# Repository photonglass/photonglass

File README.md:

日本語 | [English](README.en.md)

# PHOTON GLASS

一人称のカメラで捉えるイメージから，音などのフィードバックでユーザーにインタラクションする，メガネ型のデバイス〈PHOTON GLASS〉のハードウェアデータです。
PHOTON GLASS は、文字を読み上げるメガネOTON GLASS ver5 を元にしながら、自作の容易さや改変性を高め、ツールキットとして新しく開発したものです。
基板2枚（メイン基板・カメラ基板）の設計データ、3Dプリンターで造形できる本体とカメラユニットの筐体、電源ケーブルのカバー、本体のプログラム、組み立てとセットアップの手順を公開しています。
ここで公開しているプログラムは、PHOTON GLASS のサンプル実装のひとつです。一人称カメラで捉えた文字を読み上げる（画像から文字を認識し、音声で読み上げる）機能を実行します。

## 中身

| フォルダ | 内容 | 開けるソフト |
|---|---|---|
| [`hardware/`](hardware/README.md) | 基板2枚の概要、ファイルの開き方、元設計からの変更 | — |
| [`hardware/main-board/`](hardware/main-board) | メイン基板（Raspberry Pi Zero 2 W に載る音声・ボタン基板） | KiCad 9 以降 / Fusion（Eagle形式） |
| [`hardware/camera-board/`](hardware/camera-board) | カメラ基板（HDMIケーブルでメイン基板とつながる） | KiCad 9 以降 / Fusion（Eagle形式） |
| [`enclosure/main-body/`](enclosure/main-body) | 本体の筐体（ボディ前面・背面・側面、メインボタン、サブボタン、状態ランプのレンズ） | F3D（Fusion）/ STEP（FreeCAD など）/ STL・3MF（スライサー） |
| [`enclosure/camera-unit/`](enclosure/camera-unit) | カメラユニットの筐体・メガネ用アタッチメント | STEP（Fusion・FreeCAD など）/ STL・3MF（スライサー）/ Python（CadQuery） |
| [`enclosure/usb-power-cable/`](enclosure/usb-power-cable) | モバイルバッテリーからメイン基板へ給電するケーブルの作り方（配線・部品）と、USB プラグのカバー | STEP / STL / Python（CadQuery） |
| [`software/`](software) | 本体プログラムと効果音。普段使うのは `main_async.py`、仕組みを学ぶなら流れの読みやすい `main_seq.py`（違いは [`software/README.md`](software/README.md)） | Python 3（Raspberry Pi） |
| [`software/test/`](software/test) | 組み立て後の動作テスト用スクリプト（Raspberry Pi で実行） | Python 3 |
| [`docs/`](docs) | 組み立てガイド（[`BUILD_GUIDE.md`](docs/BUILD_GUIDE.md)）、Raspberry Pi のセットアップ（[`SETUP_RASPBERRY_PI.md`](docs/SETUP_RASPBERRY_PI.md)）、部品リスト（[`parts_list.md`](docs/parts_list.md)：データシート・回路記号の照合結果） | — |

## はじめての人へ
- **まず読む**：[`docs/BUILD_GUIDE.md`](docs/BUILD_GUIDE.md) に、発注から動かすまでの作業の順番と、それぞれで読むドキュメントをまとめています。
- **基板を作る**：[`hardware/JLCPCB_ORDERING.md`](hardware/JLCPCB_ORDERING.md) の手順で、JLCPCB に部品実装まで発注できます（ガーバー・部品表・部品配置ファイル付き）。
- **筐体を印刷する**：本体は [`enclosure/main-body/README.md`](enclosure/main-body/README.md)、カメラユニットは [`enclosure/camera-unit/README.md`](enclosure/camera-unit/README.md) に、印刷設定（Bambu Lab A1 / PETG）と組み立て手順があります。
- **Raspberry Pi を準備する**：[`docs/SETUP_RASPBERRY_PI.md`](docs/SETUP_RASPBERRY_PI.md) に、OS の書き込みから動作テスト、自動起動までの手順があります。
- **設計を変える**：基板は KiCad か Fusion で、筐体は STEP を CAD に読み込んで編集します（本体は Fusion の元データ `.f3d` もあります。カメラユニットと電源ケーブルのカバーは、`src/` の Python スクリプトの数値を変えて作り直すこともできます）。

## 質問・不具合の報告

質問や不具合の報告は、GitHub の Issues で受け付けています。
https://github.com/photonglass/photonglass/issues

## 憲法
PHOTON GLASS の理念と利用、名称、特許については、[憲法（`CHARTER.md`）](CHARTER.md)に定めています。

## ライセンス
Copyright (C) 株式会社オトングラス

対象ごとに、次のライセンスで公開しています。

| 対象 | 含まれるもの | ライセンス | 全文 |
|---|---|---|---|
| ソフトウェア | `software/` のプログラム（`main_async.py`・`main_seq.py`・`test/` など） | GNU General Public License v3.0（GPL-3.0-only） | [`LICENSE`](LICENSE) |
| ハードウェア | `hardware/`（基板の KiCad・Eagle データ、BOM・CPL、ガーバーを作るスクリプト `hardware/tools/gerbgen.py`）、`enclosure/`（筐体の CadQuery スクリプトと設計データ。本体の Fusion の元データ `.f3d` を含む）と、それらの生成物（ガーバー、STL・STEP・3MF）。**例外**：README・写真・画像と `hardware/JLCPCB_ORDERING.md` は除く（ドキュメント・写真・画像として CC BY-SA 4.0） | CERN Open Hardware Licence Version 2 - Strongly Reciprocal（CERN-OHL-S v2） | [`LICENSE-HARDWARE`](LICENSE-HARDWARE) |
| ドキュメント・写真・画像 | `docs/`、`CHARTER.md`、`CONTRIBUTING.md`、各フォルダの `README.md`、`hardware/JLCPCB_ORDERING.md`、Issue のテンプレート（`.github/ISSUE_TEMPLATE/`）、写真・画像（各フォルダの `images/` など） | クリエイティブ・コモンズ 表示-継承 4.0 国際（CC BY-SA 4.0） | 公式テキスト：[日本語](https://creativecommons.org/licenses/by-sa/4.0/legalcode.ja)・[English](https://creativecommons.org/licenses/by-sa/4.0/legalcode.en) |
| サウンド | `software/sound/` の効果音 | CC BY-SA 4.0 | 同上 |

- 各 README、写真・画像、`hardware/JLCPCB_ORDERING.md` は、`hardware/`・`enclosure/`・`software/` の中にあっても CC BY-SA 4.0 です。`software/sound/` も、`software/` の中にありますが CC BY-SA 4.0 です。
- 文書の英語版（`README.en.md`・`CHARTER.en.md`・`hardware/JLCPCB_ORDERING.en.md` など、名前の末尾が `.en.md` のファイル）も、日本語版と同じく CC BY-SA 4.0 です。

### CC BY-SA 4.0 のクレジット表記
ドキュメント・写真・画像・サウンドは、株式会社オトングラスが CC BY-SA 4.0 で提供しています。全文のファイルはこのリポジトリに入れていないので、公式テキスト（[日本語](https://creativecommons.org/licenses/by-sa/4.0/legalcode.ja)・[English](https://creativecommons.org/licenses/by-sa/4.0/legalcode.en)）を見てください。

使うときは、次のようにクレジットを表記してください。改変したときは、改変したことも書いてください。
```
PHOTON GLASS（Copyright (C) 株式会社オトングラス）
https://github.com/photonglass/photonglass
CC BY-SA 4.0 https://creativecommons.org/licenses/by-sa/4.0/
```

### かんたんな説明
正確な条件は、各ライセンスの全文を見てください。

**できること**
- 誰でも無料で、このデータで基板や筐体を作り、使い、売ることができます。
- 自由に改変できます。

**守ること**
- 作ったもの・改変したものを人に配ったり売ったりするときは、元と同じライセンスで公開する。
  - ソフトウェアとハードウェアは、受け取った人がソース（プログラム・設計データ）を手に入れられるようにする。ハードウェアの場合は、ソースを渡すか、ソースの置き場所を知らせる。
- 著作権表示とライセンスの表示を消さない。改変した場合は、いつ・どこを変えたかを書く。
- ドキュメント・写真・画像・サウンドを使うときは、上のクレジットを表記する。

**その他**
- 無保証です（作ったものが動かなくても、作者は責任を負いません）。
- 自分で使うだけなら、改変したデータを公開する義務はありません。
- 特許の扱いは、憲法の[「3. 特許について」](CHARTER.md#3-特許について)を見てください。

### 商用ライセンス
クローズドな製品への組み込みなど、各ライセンスの条件と異なる利用を希望する場合は、商用ライセンスを個別に契約できます。問い合わせはこちら：https://note.com/keisukeshimakage/n/nef3c9957ae25

### 含まれていないもの
- 部品メーカーや EasyEDA/LCSC が配布している部品の3Dモデル（再配布の条件がはっきりしないため）。基板の3D形状は KiCad や Fusion の3Dビューで確認してください。
- Google Cloud の API キー（各自で用意して、プログラムと同じフォルダの `api_key.txt` に書く。書き方は [`software/README.md`](software/README.md#動かし方)）。

### クレジット
**PHOTON GLASS（2026年）**
- 回路・基板設計、ドキュメンテーション：山中将治（Masaharu Yamanaka）
- プロダクトデザイン：小松靖知（Yasutomo Komatsu）
- プログラミング：石塚日向（Hinata Ishizuka）
- アドバイジング：須田拓也（Hiroya Suda）、高橋卓久真（Takuma Takahashi）、陳冠宇（Chen Kuan-Yu）

**OTON GLASS ver5（2019年）― PHOTON GLASSの元となったモデル**
- エンジニアリング：宮下恵太（Keita Miyashita）
- サーバーサイドエンジニアリング：鶴岡秀樹（Hideki Tsuruoka）
- プロダクトデザイン：佐野友優（Tomomasa Sano）
- サウンドデザイン：田中堅大（Kenta Tanaka）

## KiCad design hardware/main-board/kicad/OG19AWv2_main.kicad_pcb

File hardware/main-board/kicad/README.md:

日本語 | [English](README.en.md)

# KiCad 9 プロジェクト（メイン基板）

`OG19AWv2_main.kicad_pro` をダブルクリックすると、回路図と基板が開きます。
`../eagle/` の Eagle データを KiCad 9.0 で読み込んで作ったものです。
KiCad 10 以降でも開けますが、保存するとファイルが新しい形式になり、KiCad 9 では開けなくなります。

## Eagle 版との照合（2026-11-12）
| 項目 | 結果 |
|---|---|
| 接続（ネット50本、全パッド） | Eagle 版・回路図・基板の3つで一致 |
| 配線 / ビア / 外形 | 632本 / 125個 / 79 × 42 mm で Eagle 版と同じ |
| ベタ | AGND・DGND を表裏に（計4枚）、充填済み |
| DRC（クリアランス・未配線） | エラー 0 |

### 読み込み後に直したところ
- 基板のネット名を回路図のネット名にそろえた（Eagle の `N$1` などを KiCad 形式の名前に）。
- 標準のクリアランスを 0.2 → **0.15 mm** に変更（元の設計の最小間隔 6 mil = 0.1524 mm に合わせた）。
- 回路図の部品と基板のフットプリントの対応を修正（`R0603` → `R0603_334`、`C0603` → `C0603_334`）。
- 基板のフットプリントの「値」を回路図にそろえた（ボタン3個・コネクタ2個）。

### 部品番号の違い
KiCad の決まり（部品番号は「文字＋数字」）のため、いくつかの部品番号に `0` が付いています。JLCPCB 用の BOM/CPL や説明書は Eagle 版の名前のままです。
| Eagle / BOM・CPL | KiCad |
|---|---|
| PCM5102A | PCM5102A0 |
| SW_MAIN / SW_SUB / SW_UP / SW_DOWN | SW_MAIN0 / SW_SUB0 / SW_UP0 / SW_DOWN0 |
| SPK | SPK0 |
| 5V | UNK5V0 |

### 残っている警告（問題なし）
- 使っていないピンが未接続：Raspberry Pi の40ピンのうち使っていない GPIO と GND、HDMI（CN3）の 11・17・19番。元の設計どおり。
- `UNK_HOLE_0/1`：取り付け穴（非メッキ穴）。回路図に部品がないため「余計なフットプリント」と表示される。
- 40ピンの25番（AGND）の表面側サーマルのスポークが1本：裏面と配線でつながっているので問題なし。
- VR1 まわりの 0.9 mm の短い配線の切れ端：元の設計にあったもの。
- シルクの重なり・文字の大きさ：Eagle のシルク設定をそのまま引き継いだもの（JLCPCB は自動で調整する）。

## DRC の結果（2026-11-25、シルクの文字を大きくしたとき）
KiCad 9.0.8 で、すべての重要度（エラーと警告）と回路図との照合を有効にして実行しました。
| 項目 | 結果 |
|---|---|
| エラー | 1件（上の「40ピンの25番のサーマル」。前からあるもの） |
| 警告 | 83件（変更前 128件。新しく増えたものはなし） |
| 未配線 | 0 |
| 回路図との照合 | 26件（ネット名の表記の違いと取り付け穴。変更前と同じ） |

このとき、次の2つを直しました。
- 表面のシルクの「github.com/photonglass/photonglass / CERN-OHL-S v2」と「PHOTON GLASS / 2026 / PB-4」を、文字の高さ 1.0 mm・線の太さ 0.16 mm にした（JLCPCB の最小値は高さ 1.0 mm・線の太さ 0.153 mm）。Eagle のデータも同じく直してある。
- Eagle の線幅 0 の補助線（基板全体を区切る縦横の線、8本）が、KiCad では表面のシルク（線幅 0.1 mm）として読み込まれていたので、印刷されない User.Drawings レイヤーに移した。Eagle からガーバーを作るスクリプトはこの線を出力しないので、`../gerber/` の zip には元から入っていない。KiCad でガーバーを出力したときにだけ、この線が印刷されていた。

## ガーバーの出力
「ファイル → 製造用ファイル出力 → ガーバー」と「ドリルファイル」で出力し、1つの zip にまとめます。
基板を直さない場合は、`../gerber/` の zip をそのまま使ってください。
`../gerber/` の zip は、Eagle のデータからスクリプトで作ったものです（[`../../JLCPCB_ORDERING.md` の「ガーバーについて」](../../JLCPCB_ORDERING.md#ガーバーについて)）。KiCad で出力すると、ベタGNDの広がり方（基板の端や穴からの間隔）とシルクの文字の形が、この zip と少し変わります。

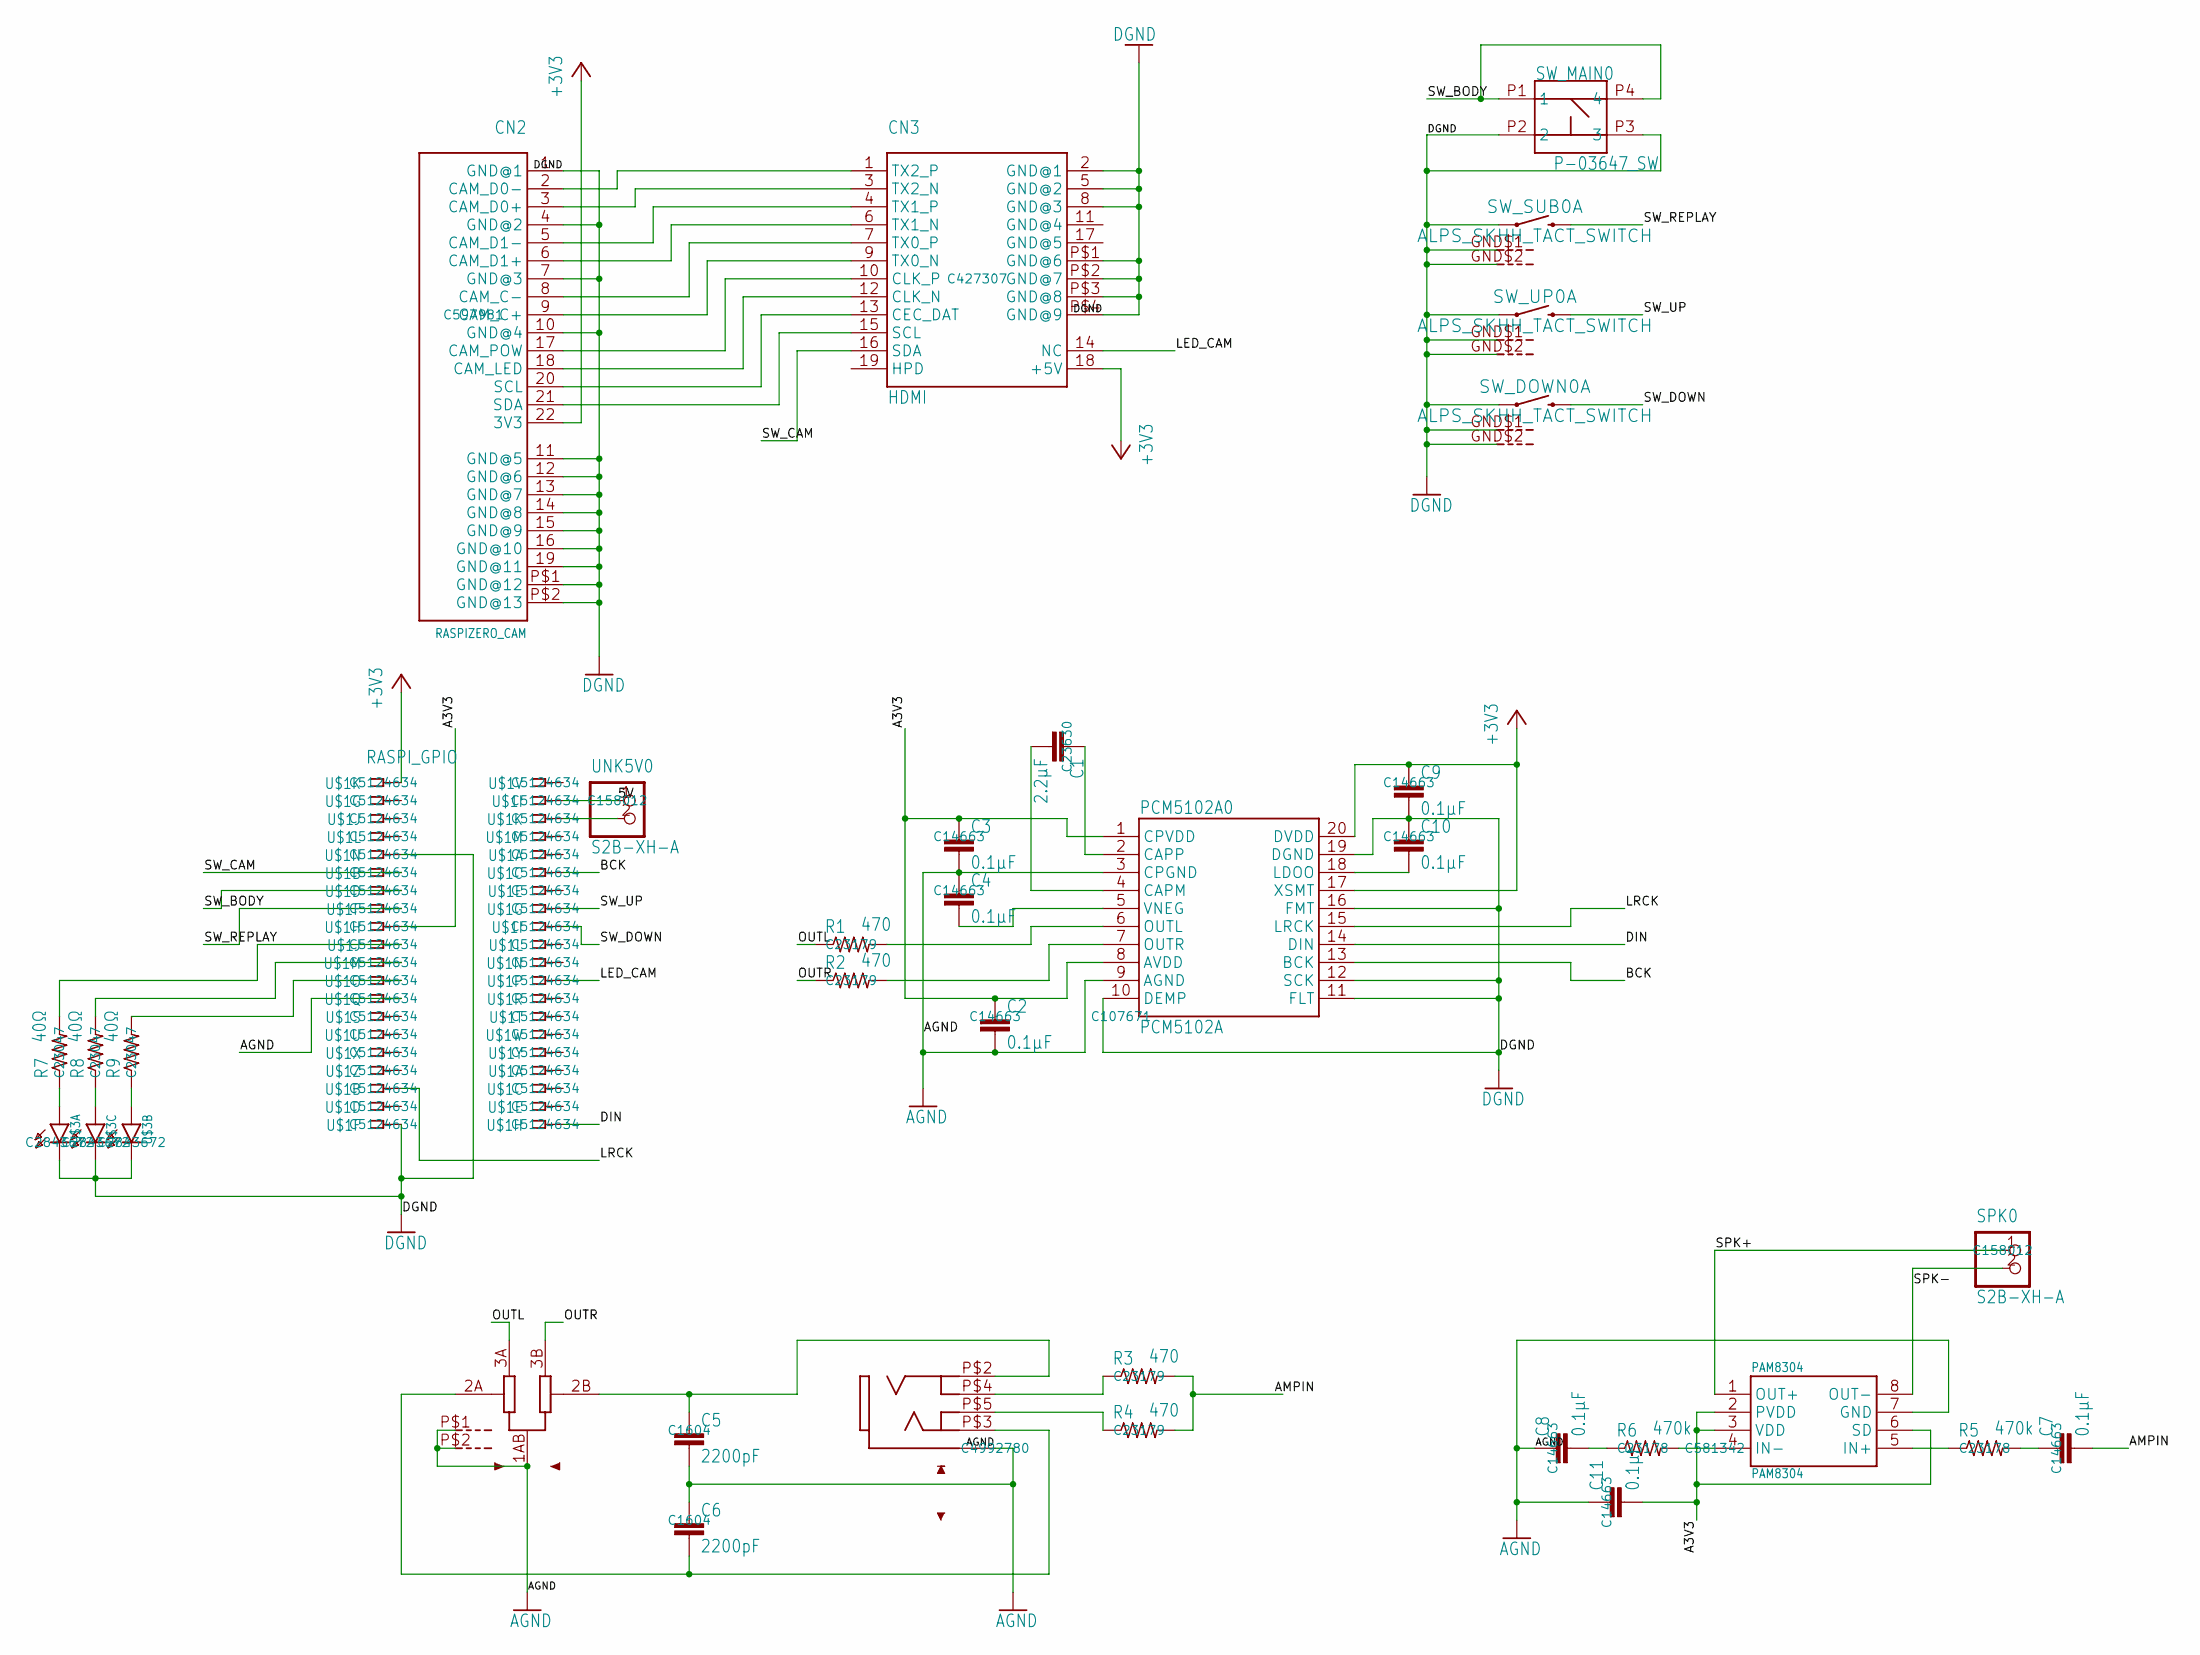
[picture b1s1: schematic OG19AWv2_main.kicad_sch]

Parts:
C1: 2.2μF; C0603_334; LCSC C23630
C2, C3, C4, C7, C8, C9, C10, C11: 0.1μF; C0603_334; LCSC C14663
C5, C6: 2200pF; C0603_334; LCSC C1604
CN1: SWICHCRAFT_3.5MM_PHONE_JACK; SJ-43516-SMT; LCSC C4992780
CN2: RASPIZERO_CAM; FH12-22S-0.5SH; LCSC C597981
CN3: HDMI; LCSC C427307
PAM8304: PAM8304; MSOP8; LCSC C581342
PCM5102A0: PCM5102A; SSOP20; LCSC C107671
R1, R2, R3, R4: 470; R0603_334; LCSC C23179
R5, R6: 470k; R0603_334; LCSC C23178
R7, R8, R9: 40Ω; R0603_334; LCSC C23047
SPK0: S2B-XH-A; B2B-XH-A; LCSC C158012
SW_DOWN0: ALPS_SKHH_TACT_SWITCH; SKHH_SIDEPUSH; MPN Alps SKHHLPA010
SW_MAIN0: P-03647_SW; SW; MPN Cosland TS-0606-F-N-RED
SW_SUB0: ALPS_SKHH_TACT_SWITCH; SKHH_SIDEPUSH; MPN Alps SKHHLPA010
SW_UP0: ALPS_SKHH_TACT_SWITCH; SKHH_SIDEPUSH; MPN Alps SKHHLPA010
U$1: RASPI_GPIO; SSW-120-02-G-D; LCSC C5124634
U$3: KPF-3236SURKMGKPBC; S6-3528RGBTA; LCSC C2843672
UNK5V0: S2B-XH-A; B2B-XH-A; LCSC C158012
VR1: ALPS_RK10J; RK10J_DIP; MPN R1001G16T2B-B10K

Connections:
+3V3: C9.1, CN2.22 (3V3), CN3.18 (+5V), PCM5102A0.17 (XSMT), PCM5102A0.20 (DVDD), U$1.1
/5V: U$1.4, UNK5V0.1
/A3V3: C2.1, C3.1, C11.2, PAM8304.2 (PVDD), PAM8304.3 (VDD), PAM8304.6 (SD), PCM5102A0.1 (CPVDD), PCM5102A0.8 (AVDD), U$1.17
/AMPIN: C7.2, R3.2, R4.2
/BCK: PCM5102A0.13 (BCK), U$1.12
/DIN: PCM5102A0.14 (DIN), U$1.40
/LED_CAM: CN3.14 (NC), U$1.24
/LRCK: PCM5102A0.15 (LRCK), U$1.35
/OUTL: R1.1, VR1.3A
/OUTR: R2.1, VR1.3B
/SPK+: PAM8304.1 (OUT+), SPK0.1
/SPK-: PAM8304.8 (OUT-), SPK0.2
/SW_BODY: SW_MAIN0.P1 (1), SW_MAIN0.P4 (4), U$1.13
/SW_CAM: CN3.16 (SDA), U$1.11
/SW_DOWN: SW_DOWN0.P$2 (2), U$1.18
/SW_REPLAY: SW_SUB0.P$2 (2), U$1.15
/SW_UP: SW_UP0.P$2 (2), U$1.16
AGND: C2.2, C3.2, C4.1, C5.2, C6.1, C8.1, C11.1, CN1.P$1, CN1.P$6, PAM8304.7 (GND), PCM5102A0.3 (CPGND), PCM5102A0.9 (AGND), U$1.25, VR1.1AB, VR1.P$1 (G), VR1.P$2 (G)
DGND: C9.2, C10.1, CN2.1 (GND@1), CN2.4 (GND@2), CN2.7 (GND@3), CN2.10 (GND@4), CN2.11 (GND@5), CN2.12 (GND@6), CN2.13 (GND@7), CN2.14 (GND@8), CN2.15 (GND@9), CN2.16 (GND@10), CN2.19 (GND@11), CN2.P$1 (GND@12), CN2.P$2 (GND@13), CN3.2 (GND@1), CN3.5 (GND@2), CN3.8 (GND@3), CN3.P$1 (GND@6), CN3.P$2 (GND@7), CN3.P$3 (GND@8), CN3.P$4 (GND@9), PCM5102A0.10 (DEMP), PCM5102A0.11 (FLT), PCM5102A0.12 (SCK), PCM5102A0.16 (FMT), PCM5102A0.19 (DGND), SW_DOWN0.GND$1 (G), SW_DOWN0.GND$2 (G), SW_DOWN0.P$1 (1), SW_MAIN0.P2 (2), SW_MAIN0.P3 (3), SW_SUB0.GND$1 (G), SW_SUB0.GND$2 (G), SW_SUB0.P$1 (1), SW_UP0.GND$1 (G), SW_UP0.GND$2 (G), SW_UP0.P$1 (1), U$1.9, U$1.39, U$3.P$1 (K), U$3.P$2 (K), U$3.P$3 (K)
unnamed: C7.1, R5.2
unnamed: C8.2, R6.1
unnamed: CN1.P$4, R3.1
unnamed: CN1.P$5, R4.1
unnamed: CN2.9 (CAM_C+), CN3.9 (TX0_N)
unnamed: CN2.8 (CAM_C-), CN3.7 (TX0_P)
unnamed: CN2.3 (CAM_D0+), CN3.3 (TX2_N)
unnamed: CN2.2 (CAM_D0-), CN3.1 (TX2_P)
unnamed: CN2.6 (CAM_D1+), CN3.6 (TX1_N)
unnamed: CN2.5 (CAM_D1-), CN3.4 (TX1_P)
unnamed: CN2.18 (CAM_LED), CN3.12 (CLK_N)
unnamed: CN2.17 (CAM_POW), CN3.10 (CLK_P)
unnamed: CN2.20 (SCL), CN3.13 (CEC_DAT)
unnamed: CN2.21 (SDA), CN3.15 (SCL)
unnamed: PAM8304.5 (IN+), R5.1
unnamed: PAM8304.4 (IN-), R6.2
unnamed: C1.2, PCM5102A0.4 (CAPM)
unnamed: C1.1, PCM5102A0.2 (CAPP)
unnamed: C10.2, PCM5102A0.18 (LDOO)
unnamed: PCM5102A0.6 (OUTL), R1.2
unnamed: PCM5102A0.7 (OUTR), R2.2
unnamed: C4.2, PCM5102A0.5 (VNEG)
unnamed: U$1.6, UNK5V0.2
unnamed: R7.2, U$1.19
unnamed: R8.2, U$1.21
unnamed: R9.2, U$1.23
unnamed: R7.1, U$3.P$4 (A)
unnamed: R9.1, U$3.P$6 (A)
unnamed: R8.1, U$3.P$5 (A)
unnamed: C6.2, CN1.P$3, VR1.2A
unnamed: C5.1, CN1.P$2, VR1.2B

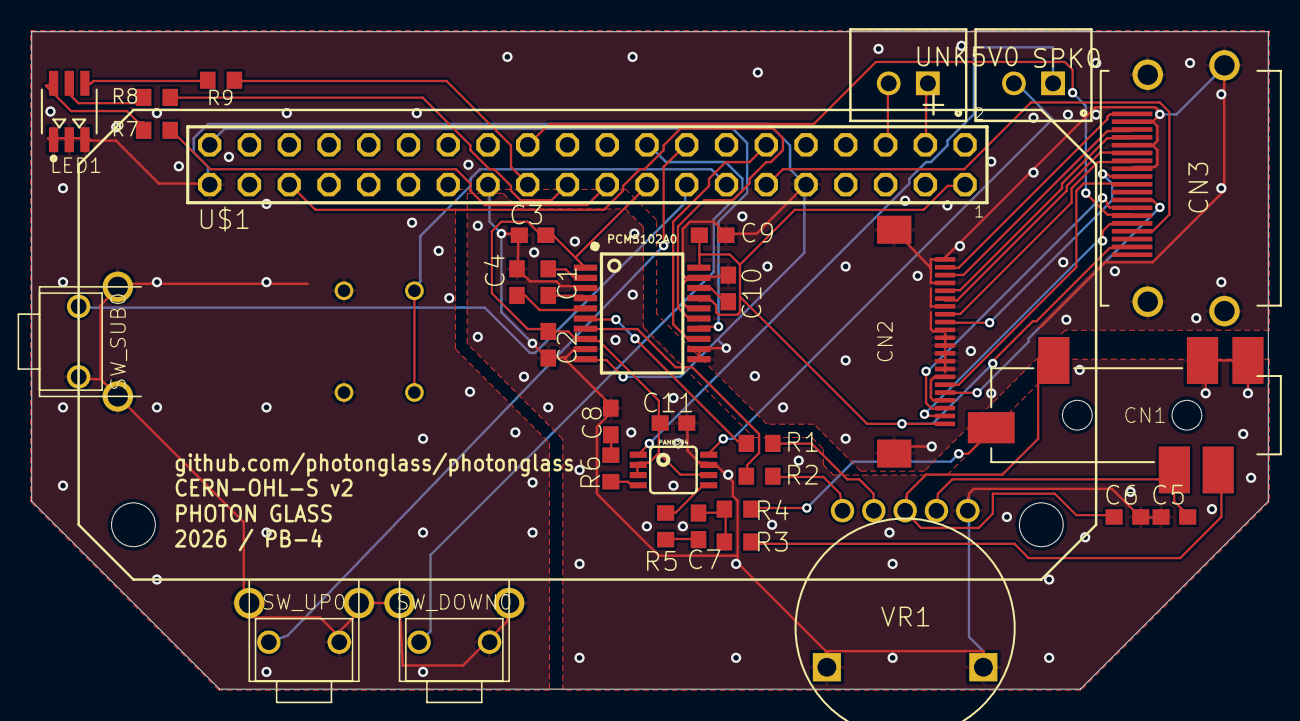
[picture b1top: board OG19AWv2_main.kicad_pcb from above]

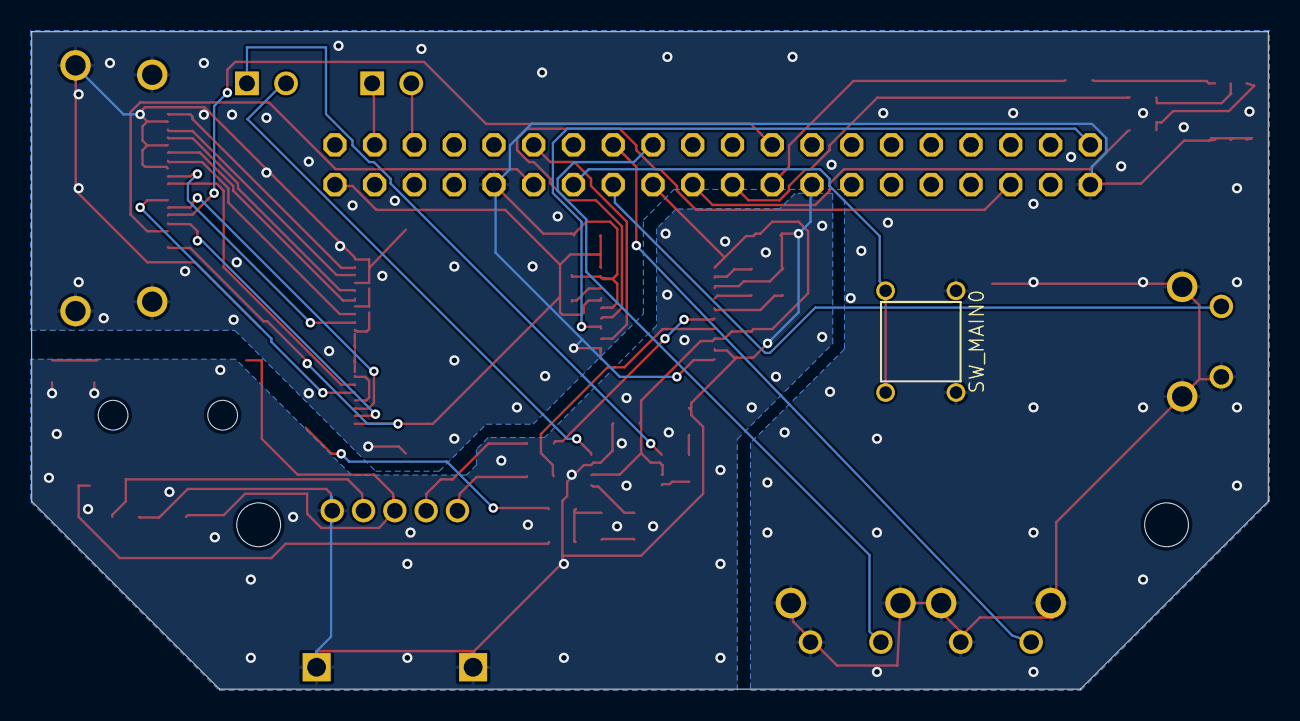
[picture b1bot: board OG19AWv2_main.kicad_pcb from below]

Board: 2 copper layers, 79.0 x 42.0 mm, 36 parts (2 on the bottom side), 50 nets.

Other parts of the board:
UNK_HOLE_0: dummyfp0
UNK_HOLE_1: dummyfp1

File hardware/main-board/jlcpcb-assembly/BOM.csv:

Comment,Designator,Footprint,JLCPCB Part #（optional）,Manufacturer Part,Library Type,Stock (checked 2026-10-14),Note
2.2μF,C1,0603,C23630,Samsung Electro-Mechanics CL10A225KO8NNNC,Basic,3391639,
2200pF,"C5,C6",0603,C1604,FH (Guangdong Fenghua Advanced Tech) 0603B222K500NT,Basic,982010,X7R。音質重視なら C0G の C33353 (Extended) に変更可
0.1μF,"C10,C11,C2,C3,C4,C7,C8,C9",0603,C14663,YAGEO CC0603KRX7R9BB104,Basic,40021582,
SWICHCRAFT_3.5MM_PHONE_JACK,CN1,SMD,C4992780,CUI SJ-43516-SMT-TR,Extended,136,代替: 元 Switchcraft 35RASMT4BHNTRX (在庫0)。フットプリント変更・配線修正済み
RASPIZERO_CAM,CN2,"SMD,P=0.5mm,Surface Mount，Right Angle",C597981,HRS(Hirose) FH12-22S-0.5SH(55),Extended,640,
HDMI,CN3,SMD,C427307,Amphenol ICC 10029449-111RLF,Extended,1503,元部品と同系列 (Amphenol 10029449)
PAM8304,PAM8304,MSOP-8,C581342,Diodes Incorporated PAM8304ASR,Extended,2644,PAM8304ASR = MSOP-8 (ピン配置一致確認済み)
PCM5102A,PCM5102A,TSSOP-20,C107671,Texas Instruments PCM5102APWR,Extended,3701,
470,"R1,R2,R3,R4",0603,C23179,UNI-ROYAL(Uniroyal Elec) 0603WAF4700T5E,Basic,5483823,
470k,"R5,R6",0603,C23178,UNI-ROYAL(Uniroyal Elec) 0603WAF4703T5E,Basic,1243118,
40Ω,"R7,R8,R9",0603,C23047,UNI-ROYAL(Uniroyal Elec) 0603WAF402JT5E,Extended,23804,40Ω 指定。40Ω ちょうどの在庫品がないため 40.2Ω ±1%（差 0.5%、部品の許容差内）
RASPI_GPIO,U$1,"Plugin,P=2.54mm",C5124634,BOOMELE(Boom Precision Elec) 2.54-2*20P,Extended,8609,代替: 元 Samtec SSW-120-02-G-D (在庫5・高価)。汎用2x20ピンソケット 8.5mm
KPF-3236SURKMGKPBC,U$3,SMD3528-6P,C2843672,TUOZHAN S6-3528RGBTA,Extended,6388,代替: 元 Kingbright KPF-3236SURKMGKPBC (JLC未登録)。フットプリント変更、色の割当が変化

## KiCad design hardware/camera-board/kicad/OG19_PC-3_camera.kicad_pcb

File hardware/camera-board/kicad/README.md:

日本語 | [English](README.en.md)

# KiCad 9 プロジェクト（カメラ基板）

`OG19_PC-3_camera.kicad_pro` をダブルクリックすると、回路図と基板が開きます。
`../eagle/` の Eagle データを KiCad 9.0 で読み込んで作ったものです。
KiCad 10 以降でも開けますが、保存するとファイルが新しい形式になり、KiCad 9 では開けなくなります。

## Eagle 版との照合（2026-11-12）
| 項目 | 結果 |
|---|---|
| 接続（ネット16本、全パッド） | Eagle 版・回路図・基板の3つで一致 |
| 配線 / ビア / 外形 | 201本 / 52個 / 39.3 × 17.2 mm で Eagle 版と同じ |
| DRC（クリアランス・未配線） | エラー 0（GND ベタ充填済み） |

### 読み込み後に直したところ
- 基板のネット名を回路図のネット名にそろえた（Eagle の `N$1` などを KiCad 形式の名前に）。
- 標準のクリアランスを 0.2 → **0.15 mm** に変更（元の設計の最小間隔 6 mil = 0.1524 mm に合わせた）。
- 回路図の部品と基板のフットプリントの対応を修正（`R0603` → `R0603_348`、`CHIPLED_0603` → `CHIPLED_0603_259`）。
- 状態表示 LED の部品番号は、KiCad の決まりで `GND` → **`GND0`** に変わっています（JLCPCB 用の BOM/CPL では `GND` のまま）。

### 残っている警告（問題なし）
- HDMI（CN1）の 17番（DDC/CEC GND）と 19番（HPD）が未接続：元の設計どおり。
- `UNK_HOLE_0/1`：基板の取り付け穴（非メッキ穴）。回路図に部品がないため「余計なフットプリント」と表示される。
- シルク文字の大きさ・太さ：Eagle の文字設定をそのまま引き継いだもの。
- 電源ピンが駆動されていない（ERC）：回路図に PWR_FLAG がないため。動作には関係なし。

## ガーバーの出力
「ファイル → 製造用ファイル出力 → ガーバー」と「ドリルファイル」で出力し、1つの zip にまとめます。
基板を直さない場合は、`../gerber/` の zip をそのまま使ってください。
`../gerber/` の zip は、Eagle のデータからスクリプトで作ったものです（[`../../JLCPCB_ORDERING.md` の「ガーバーについて」](../../JLCPCB_ORDERING.md#ガーバーについて)）。KiCad で出力すると、ベタGNDの広がり方（基板の端や穴からの間隔）とシルクの文字の形が、この zip と少し変わります。

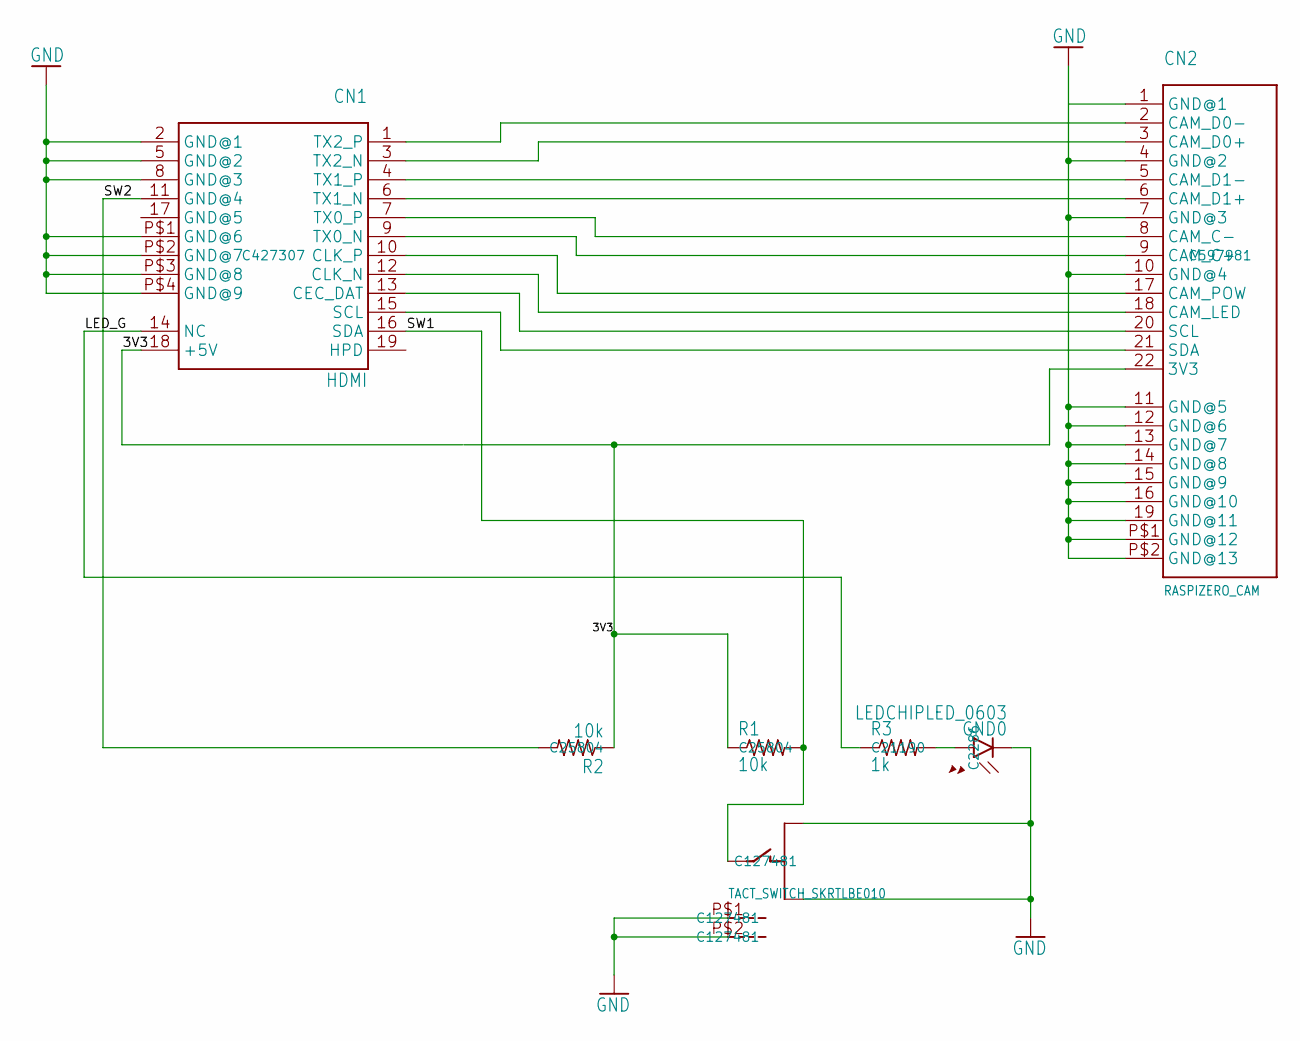
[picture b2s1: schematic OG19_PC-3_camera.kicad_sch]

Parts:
CN1: HDMI; LCSC C427307
CN2: RASPIZERO_CAM; FH12-22S-0.5SH; LCSC C597981
GND0: LEDCHIPLED_0603; CHIPLED_0603_259; LCSC C2286
R1, R2: 10k; R0603_348; LCSC C25804
R3: 1k; R0603_348; LCSC C21190
SW1: TACT_SWITCH_SKRTLBE010; SKRTLBE010; LCSC C127481

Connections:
/3V3: CN1.18 (+5V), CN2.22 (3V3), R1.1, R2.1
/LED_G: CN1.14 (NC), R3.1
/SW1: CN1.16 (SDA), R1.2, SW1.P$4 (2)
/SW2: CN1.11 (GND@4), R2.2
GND: CN1.2 (GND@1), CN1.5 (GND@2), CN1.8 (GND@3), CN1.P$1 (GND@6), CN1.P$2 (GND@7), CN1.P$3 (GND@8), CN1.P$4 (GND@9), CN2.1 (GND@1), CN2.4 (GND@2), CN2.7 (GND@3), CN2.10 (GND@4), CN2.11 (GND@5), CN2.12 (GND@6), CN2.13 (GND@7), CN2.14 (GND@8), CN2.15 (GND@9), CN2.16 (GND@10), CN2.19 (GND@11), CN2.P$1 (GND@12), CN2.P$2 (GND@13), GND0.C, SW1.P$1 (G), SW1.P$2 (G), SW1.P$3 (1), SW1.P$5 (3)
unnamed: CN1.13 (CEC_DAT), CN2.20 (SCL)
unnamed: CN1.12 (CLK_N), CN2.18 (CAM_LED)
unnamed: CN1.10 (CLK_P), CN2.17 (CAM_POW)
unnamed: CN1.15 (SCL), CN2.21 (SDA)
unnamed: CN1.9 (TX0_N), CN2.9 (CAM_C+)
unnamed: CN1.7 (TX0_P), CN2.8 (CAM_C-)
unnamed: CN1.6 (TX1_N), CN2.6 (CAM_D1+)
unnamed: CN1.4 (TX1_P), CN2.5 (CAM_D1-)
unnamed: CN1.3 (TX2_N), CN2.3 (CAM_D0+)
unnamed: CN1.1 (TX2_P), CN2.2 (CAM_D0-)
unnamed: GND0.A, R3.2

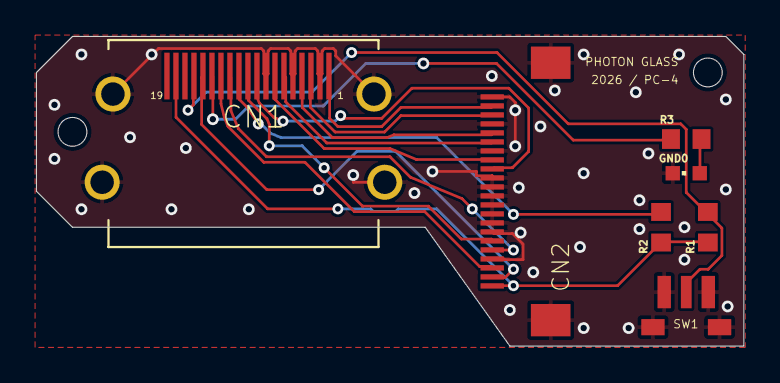
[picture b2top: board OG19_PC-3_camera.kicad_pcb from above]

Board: 2 copper layers, 39.3 x 17.2 mm, 9 parts (0 on the bottom side), 16 nets.

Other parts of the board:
UNK_HOLE_0: dummyfp0
UNK_HOLE_1: dummyfp1

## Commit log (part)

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2026-06-25 はじめに公開するファイルたち
